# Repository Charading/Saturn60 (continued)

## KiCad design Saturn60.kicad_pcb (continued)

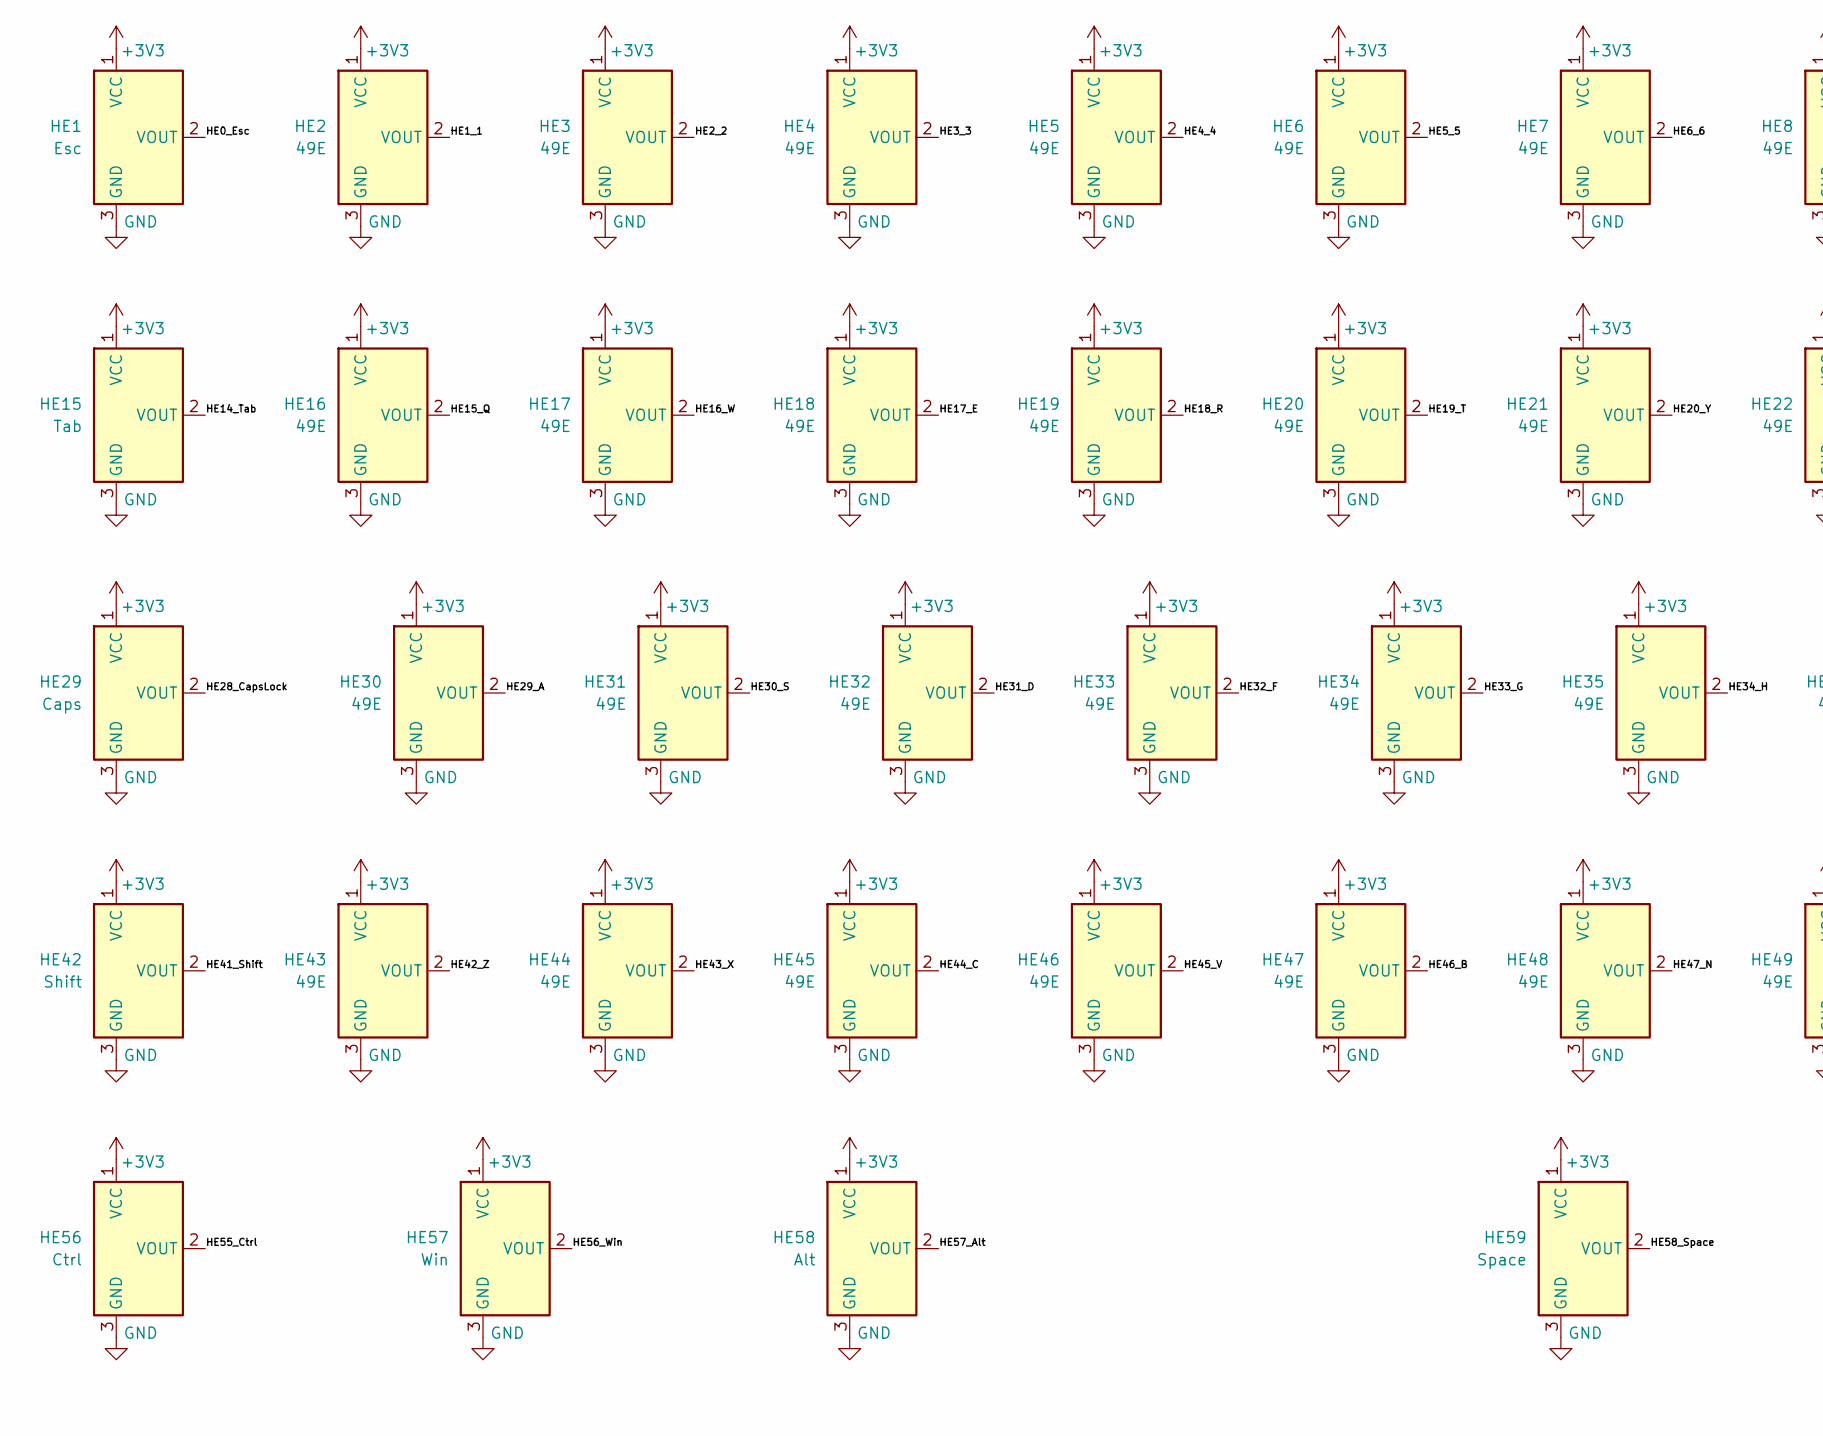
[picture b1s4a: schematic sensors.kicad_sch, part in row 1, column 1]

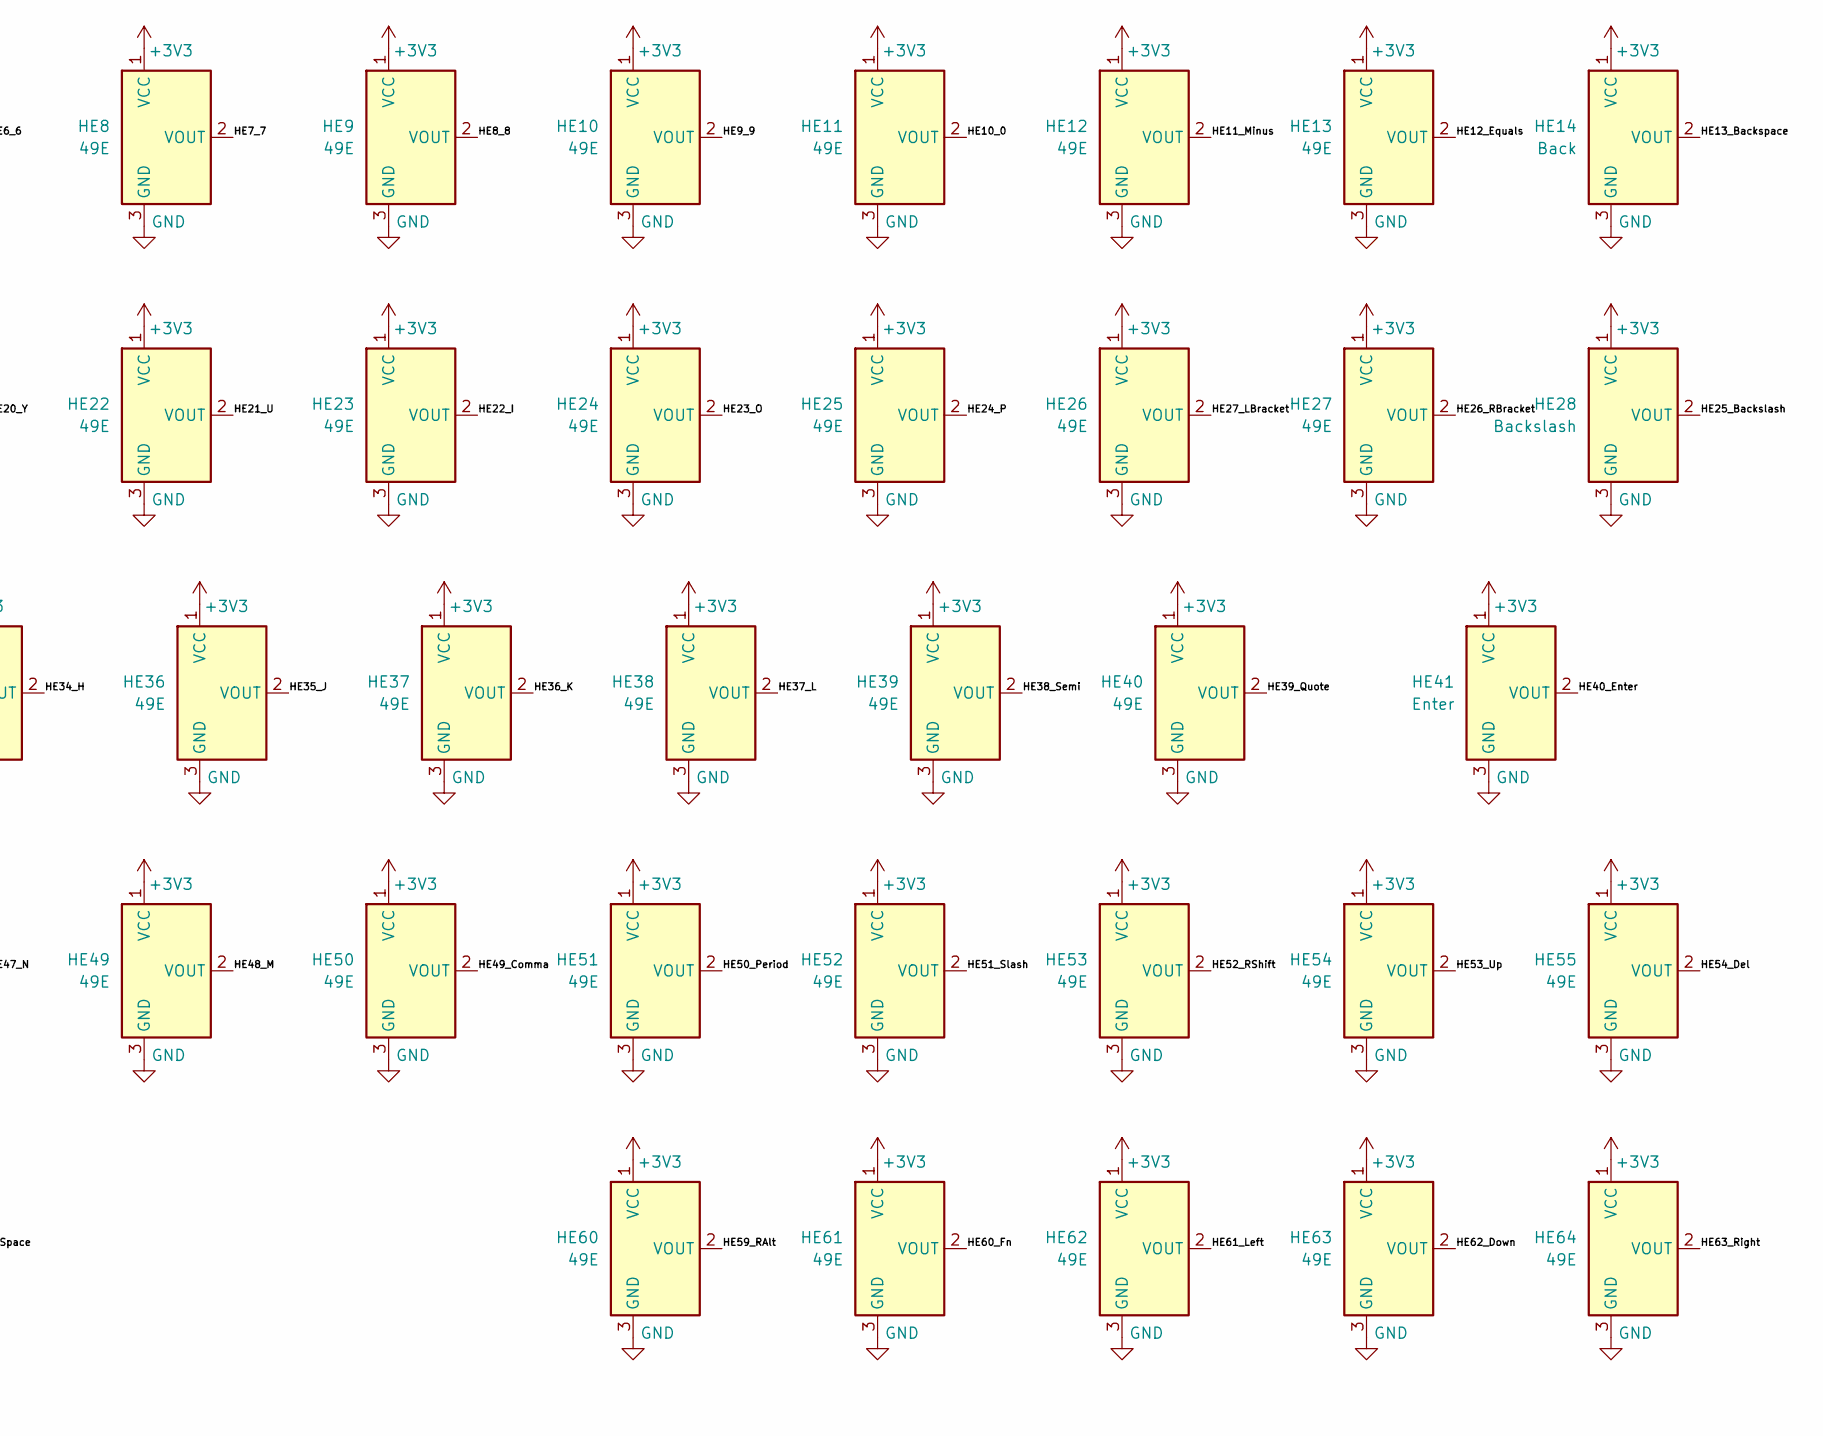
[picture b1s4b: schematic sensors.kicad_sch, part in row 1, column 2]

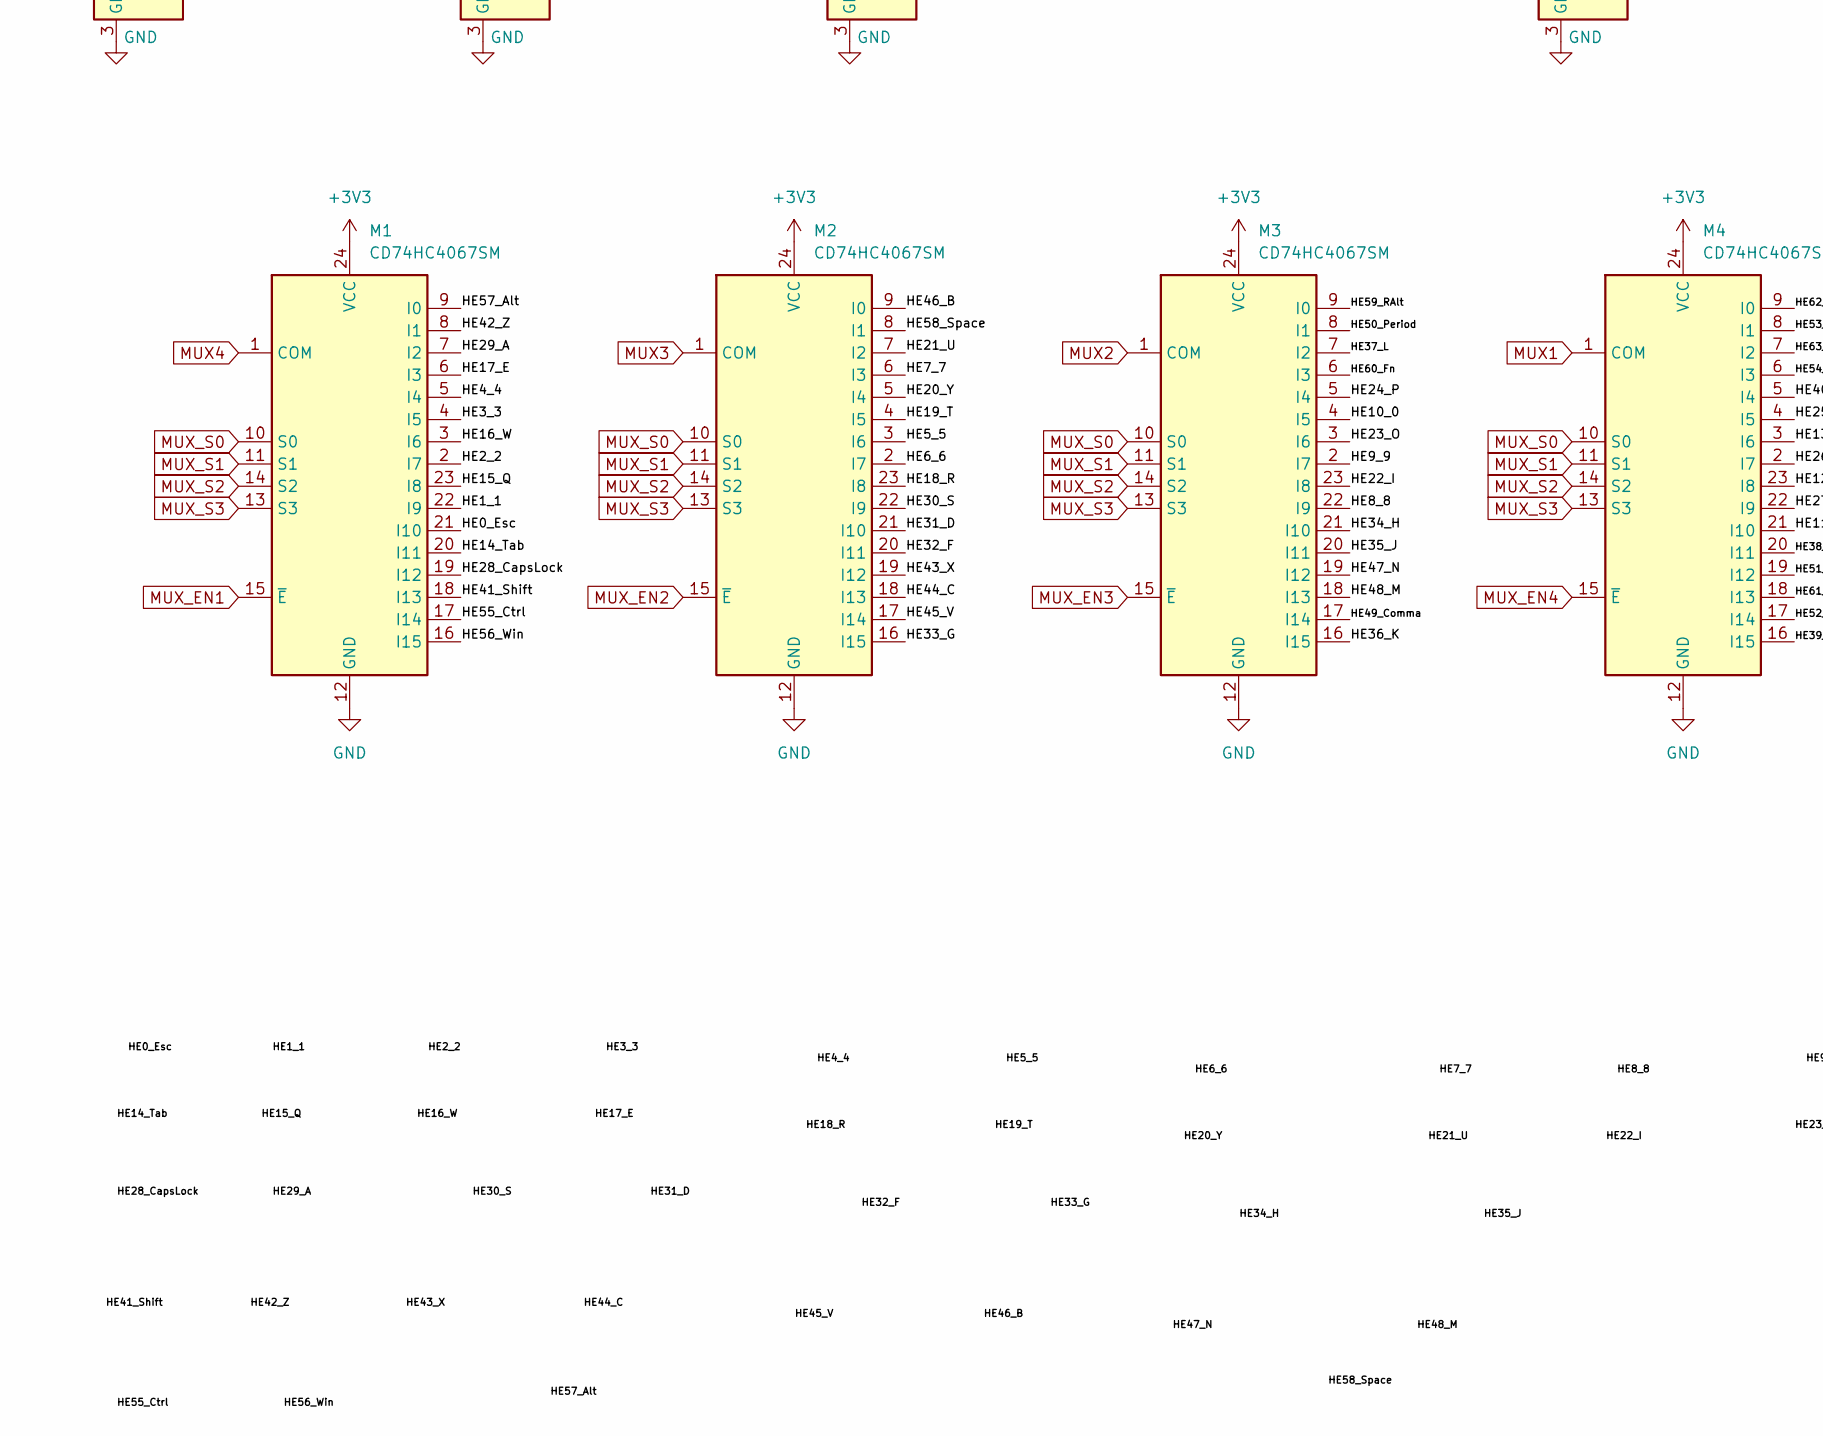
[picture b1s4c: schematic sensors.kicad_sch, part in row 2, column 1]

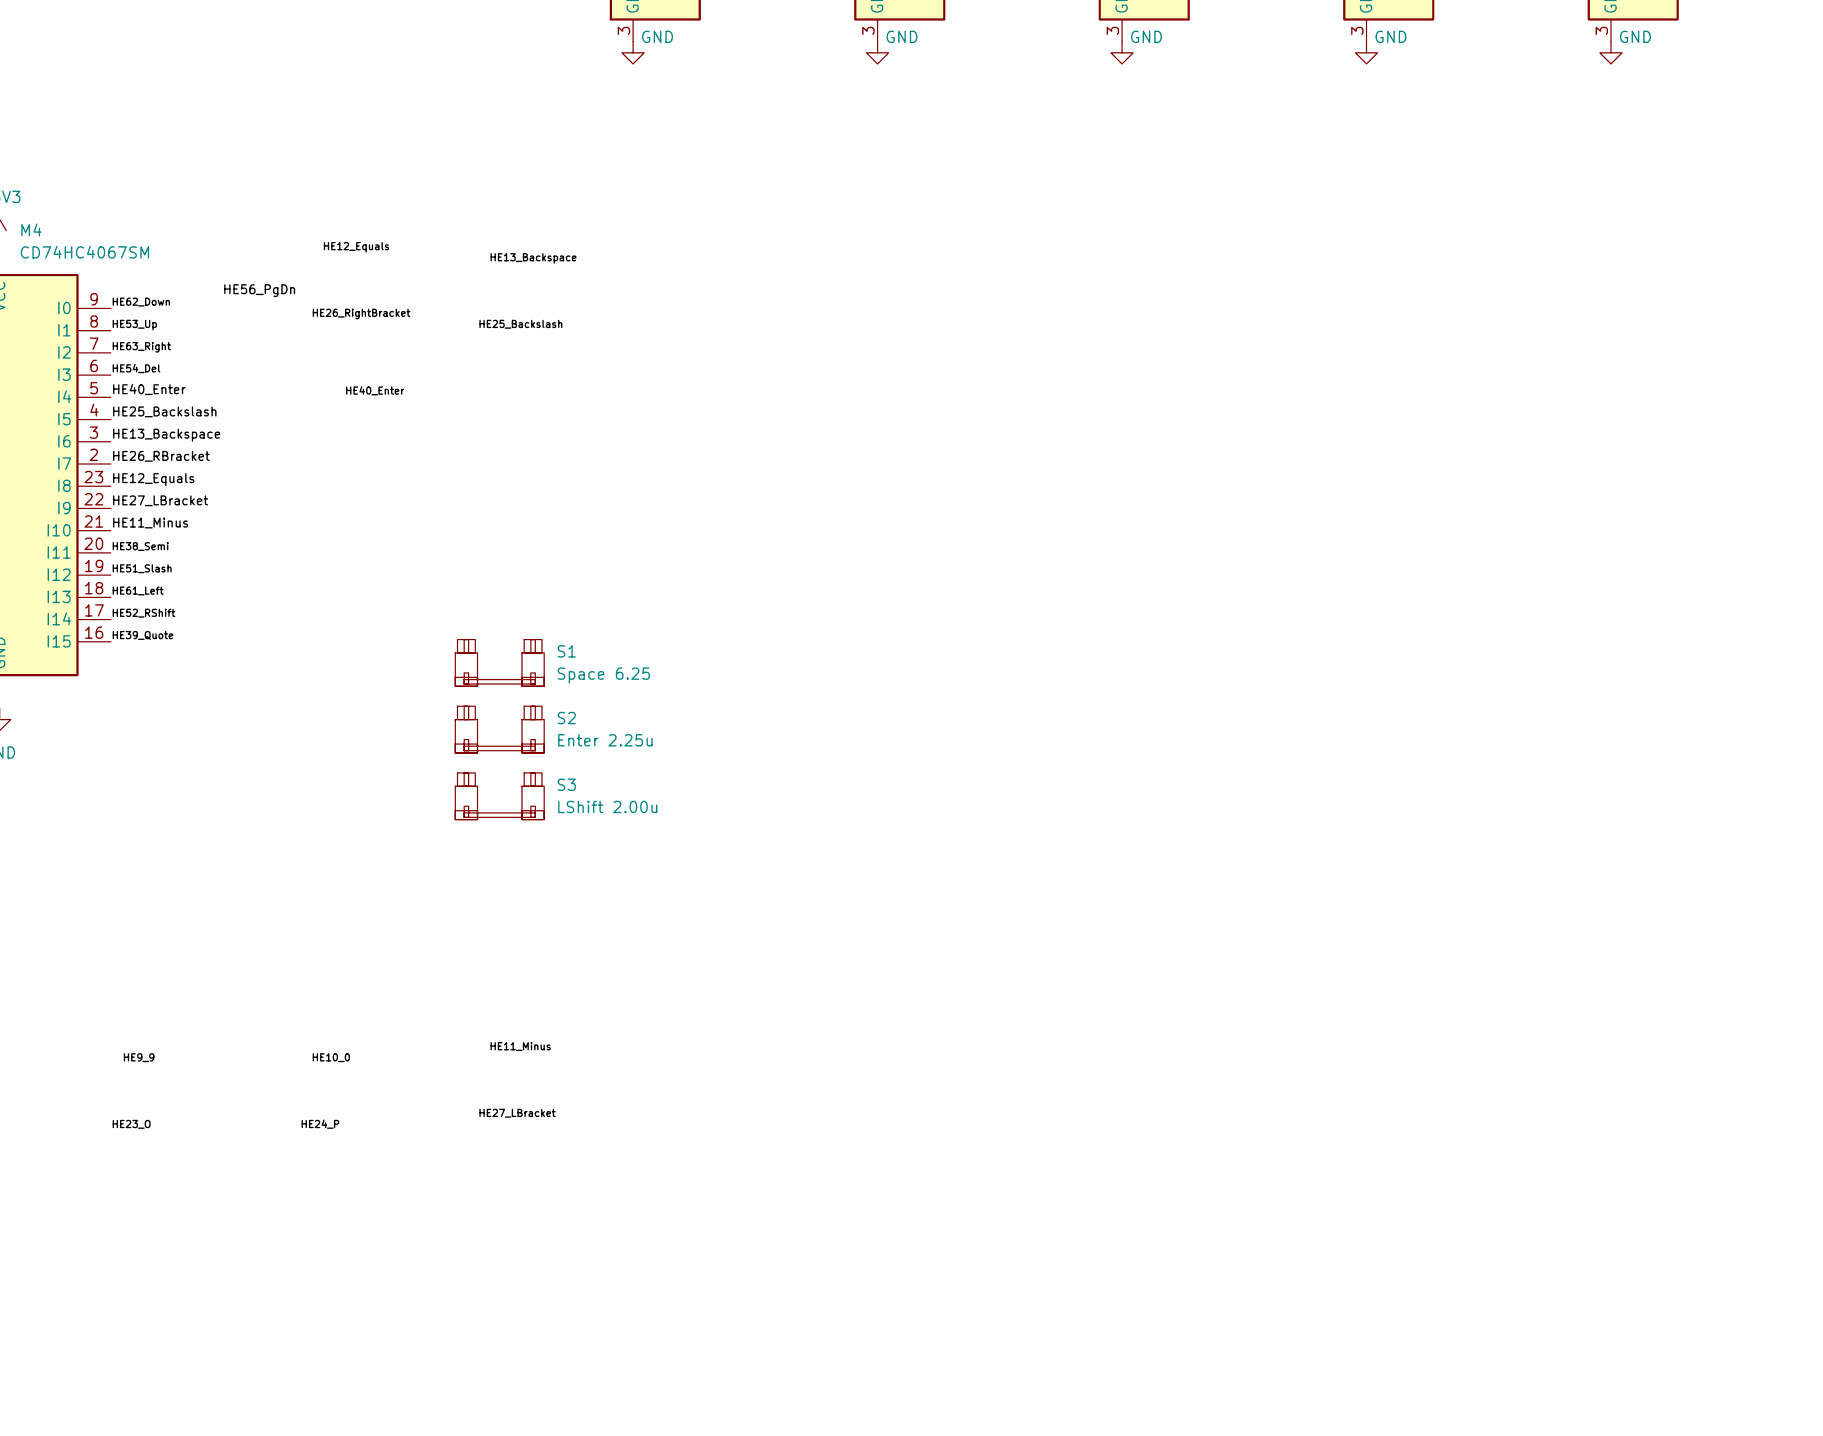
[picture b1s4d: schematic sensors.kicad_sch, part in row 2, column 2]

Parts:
HE1: Esc; SW_MX_HE_90deg_1u_Rules; LCSC C7420984
HE2, HE3, HE4, HE5, HE6, HE7, HE8, HE9, HE10, HE11, HE12, HE13, HE16, HE17, HE18, HE19, HE20, HE21, HE22, HE23, HE24, HE25, HE26, HE27, HE30, HE31, HE32, HE33, HE34, HE35, HE36, HE37, HE38, HE39, HE40, HE43, HE44, HE45, HE46, HE47, HE48, HE49, HE50, HE51, HE52, HE53, HE54, HE55, HE60, HE61, HE62, HE63, HE64: 49E; SW_MX_HE_90deg_1u_Rules; LCSC C7420984
HE14: Back; SW_MX_HE_90deg_1u_Rules; LCSC C7420984
HE15: Tab; SW_MX_HE_90deg_1.5u_Rules; LCSC C7420984
HE28: Backslash; SW_MX_HE_90deg_1.5u_Rules; LCSC C7420984
HE29: Caps; SW_MX_HE_90deg_1.75u_Rules; LCSC C7420984
HE41: Enter; SW_MX_HE_90deg_2.25u_Rules; LCSC C7420984
HE42: Shift; SW_MX_HE_90deg_2.00u_Rules; LCSC C7420984
HE56: Ctrl; SW_MX_HE_90deg_1.25u_Rules; LCSC C7420984
HE57: Win; SW_MX_HE_90deg_1.25u_Rules; LCSC C7420984
HE58: Alt; SW_MX_HE_90deg_1.25u_Rules; LCSC C7420984
HE59: Space; SW_MX_HE_90deg_6.25u_Rules; LCSC C7420984
M1, M2, M3, M4: CD74HC4067SM; SSOP-24_5.3x8.2mm_P0.65mm
S1: Space 6.25; STAB_MX_P_6.25u
S2: Enter 2.25u; STAB_MX_P_2.25u
S3: LShift 2.00u; STAB_MX_P_2u

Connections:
+3V3: HE1.1 (VCC), HE2.1 (VCC), HE3.1 (VCC), HE4.1 (VCC), HE5.1 (VCC), HE6.1 (VCC), HE7.1 (VCC), HE8.1 (VCC), HE9.1 (VCC), HE10.1 (VCC), HE11.1 (VCC), HE12.1 (VCC), HE13.1 (VCC), HE14.1 (VCC), HE15.1 (VCC), HE16.1 (VCC), HE17.1 (VCC), HE18.1 (VCC), HE19.1 (VCC), HE20.1 (VCC), HE21.1 (VCC), HE22.1 (VCC), HE23.1 (VCC), HE24.1 (VCC), HE25.1 (VCC), HE26.1 (VCC), HE27.1 (VCC), HE28.1 (VCC), HE29.1 (VCC), HE30.1 (VCC), HE31.1 (VCC), HE32.1 (VCC), HE33.1 (VCC), HE34.1 (VCC), HE35.1 (VCC), HE36.1 (VCC), HE37.1 (VCC), HE38.1 (VCC), HE39.1 (VCC), HE40.1 (VCC), HE41.1 (VCC), HE42.1 (VCC), HE43.1 (VCC), HE44.1 (VCC), HE45.1 (VCC), HE46.1 (VCC), HE47.1 (VCC), HE48.1 (VCC), HE49.1 (VCC), HE50.1 (VCC), HE51.1 (VCC), HE52.1 (VCC), HE53.1 (VCC), HE54.1 (VCC), HE55.1 (VCC), HE56.1 (VCC), HE57.1 (VCC), HE58.1 (VCC), HE59.1 (VCC), HE60.1 (VCC), HE61.1 (VCC), HE62.1 (VCC), HE63.1 (VCC), HE64.1 (VCC), M1.24 (VCC), M2.24 (VCC), M3.24 (VCC), M4.24 (VCC); also elsewhere on the board
/sensors/HE0_Esc: HE1.2 (VOUT), M1.21 (I10)
/sensors/HE1_1: HE2.2 (VOUT), M1.22 (I9)
/sensors/HE2_2: HE3.2 (VOUT), M1.2 (I7)
/sensors/HE3_3: HE4.2 (VOUT), M1.4 (I5)
/sensors/HE4_4: HE5.2 (VOUT), M1.5 (I4)
/sensors/HE5_5: HE6.2 (VOUT), M2.3 (I6)
/sensors/HE6_6: HE7.2 (VOUT), M2.2 (I7)
/sensors/HE7_7: HE8.2 (VOUT), M2.6 (I3)
/sensors/HE8_8: HE9.2 (VOUT), M3.22 (I9)
/sensors/HE9_9: HE10.2 (VOUT), M3.2 (I7)
/sensors/HE10_0: HE11.2 (VOUT), M3.4 (I5)
/sensors/HE11_Minus: HE12.2 (VOUT), M4.21 (I10)
/sensors/HE12_Equals: HE13.2 (VOUT), M4.23 (I8)
/sensors/HE13_Backspace: HE14.2 (VOUT), M4.3 (I6)
/sensors/HE14_Tab: HE15.2 (VOUT), M1.20 (I11)
/sensors/HE15_Q: HE16.2 (VOUT), M1.23 (I8)
/sensors/HE16_W: HE17.2 (VOUT), M1.3 (I6)
/sensors/HE17_E: HE18.2 (VOUT), M1.6 (I3)
/sensors/HE18_R: HE19.2 (VOUT), M2.23 (I8)
/sensors/HE19_T: HE20.2 (VOUT), M2.4 (I5)
/sensors/HE20_Y: HE21.2 (VOUT), M2.5 (I4)
/sensors/HE21_U: HE22.2 (VOUT), M2.7 (I2)
/sensors/HE22_I: HE23.2 (VOUT), M3.23 (I8)
/sensors/HE23_O: HE24.2 (VOUT), M3.3 (I6)
/sensors/HE24_P: HE25.2 (VOUT), M3.5 (I4)
/sensors/HE25_Backslash: HE28.2 (VOUT), M4.4 (I5)
/sensors/HE26_RBracket: HE27.2 (VOUT), M4.2 (I7)
/sensors/HE27_LBracket: HE26.2 (VOUT), M4.22 (I9)
/sensors/HE28_CapsLock: HE29.2 (VOUT), M1.19 (I12)
/sensors/HE29_A: HE30.2 (VOUT), M1.7 (I2)
/sensors/HE30_S: HE31.2 (VOUT), M2.22 (I9)
/sensors/HE31_D: HE32.2 (VOUT), M2.21 (I10)
/sensors/HE32_F: HE33.2 (VOUT), M2.20 (I11)
/sensors/HE33_G: HE34.2 (VOUT), M2.16 (I15)
/sensors/HE34_H: HE35.2 (VOUT), M3.21 (I10)
/sensors/HE35_J: HE36.2 (VOUT), M3.20 (I11)
/sensors/HE36_K: HE37.2 (VOUT), M3.16 (I15)
/sensors/HE37_L: HE38.2 (VOUT), M3.7 (I2)
/sensors/HE38_Semi: HE39.2 (VOUT), M4.20 (I11)
/sensors/HE39_Quote: HE40.2 (VOUT), M4.16 (I15)
/sensors/HE40_Enter: HE41.2 (VOUT), M4.5 (I4)
/sensors/HE41_Shift: HE42.2 (VOUT), M1.18 (I13)
/sensors/HE42_Z: HE43.2 (VOUT), M1.8 (I1)
/sensors/HE43_X: HE44.2 (VOUT), M2.19 (I12)
/sensors/HE44_C: HE45.2 (VOUT), M2.18 (I13)
/sensors/HE45_V: HE46.2 (VOUT), M2.17 (I14)
/sensors/HE46_B: HE47.2 (VOUT), M2.9 (I0)
/sensors/HE47_N: HE48.2 (VOUT), M3.19 (I12)
/sensors/HE48_M: HE49.2 (VOUT), M3.18 (I13)
/sensors/HE49_Comma: HE50.2 (VOUT), M3.17 (I14)
/sensors/HE50_Period: HE51.2 (VOUT), M3.8 (I1)
/sensors/HE51_Slash: HE52.2 (VOUT), M4.19 (I12)
/sensors/HE52_RShift: HE53.2 (VOUT), M4.17 (I14)
/sensors/HE53_Up: HE54.2 (VOUT), M4.8 (I1)
/sensors/HE54_Del: HE55.2 (VOUT), M4.6 (I3)
/sensors/HE55_Ctrl: HE56.2 (VOUT), M1.17 (I14)
/sensors/HE56_Win: HE57.2 (VOUT), M1.16 (I15)
/sensors/HE57_Alt: HE58.2 (VOUT), M1.9 (I0)
/sensors/HE58_Space: HE59.2 (VOUT), M2.8 (I1)
/sensors/HE59_RAlt: HE60.2 (VOUT), M3.9 (I0)
/sensors/HE60_Fn: HE61.2 (VOUT), M3.6 (I3)
/sensors/HE61_Left: HE62.2 (VOUT), M4.18 (I13)
/sensors/HE62_Down: HE63.2 (VOUT), M4.9 (I0)
/sensors/HE63_Right: HE64.2 (VOUT), M4.7 (I2)
GND: HE1.3 (GND), HE2.3 (GND), HE3.3 (GND), HE4.3 (GND), HE5.3 (GND), HE6.3 (GND), HE7.3 (GND), HE8.3 (GND), HE9.3 (GND), HE10.3 (GND), HE11.3 (GND), HE12.3 (GND), HE13.3 (GND), HE14.3 (GND), HE15.3 (GND), HE16.3 (GND), HE17.3 (GND), HE18.3 (GND), HE19.3 (GND), HE20.3 (GND), HE21.3 (GND), HE22.3 (GND), HE23.3 (GND), HE24.3 (GND), HE25.3 (GND), HE26.3 (GND), HE27.3 (GND), HE28.3 (GND), HE29.3 (GND), HE30.3 (GND), HE31.3 (GND), HE32.3 (GND), HE33.3 (GND), HE34.3 (GND), HE35.3 (GND), HE36.3 (GND), HE37.3 (GND), HE38.3 (GND), HE39.3 (GND), HE40.3 (GND), HE41.3 (GND), HE42.3 (GND), HE43.3 (GND), HE44.3 (GND), HE45.3 (GND), HE46.3 (GND), HE47.3 (GND), HE48.3 (GND), HE49.3 (GND), HE50.3 (GND), HE51.3 (GND), HE52.3 (GND), HE53.3 (GND), HE54.3 (GND), HE55.3 (GND), HE56.3 (GND), HE57.3 (GND), HE58.3 (GND), HE59.3 (GND), HE60.3 (GND), HE61.3 (GND), HE62.3 (GND), HE63.3 (GND), HE64.3 (GND), M1.12 (GND), M2.12 (GND), M3.12 (GND), M4.12 (GND); also elsewhere on the board
MUX1: M4.1 (COM); also elsewhere on the board
MUX2: M3.1 (COM); also elsewhere on the board
MUX3: M2.1 (COM); also elsewhere on the board
MUX4: M1.1 (COM); also elsewhere on the board
MUX_EN1: M1.15 (~E); also elsewhere on the board
MUX_EN2: M2.15 (~E); also elsewhere on the board
MUX_EN3: M3.15 (~E); also elsewhere on the board
MUX_EN4: M4.15 (~E); also elsewhere on the board
MUX_S0: M1.10 (S0), M2.10 (S0), M3.10 (S0), M4.10 (S0); also elsewhere on the board
MUX_S1: M1.11 (S1), M2.11 (S1), M3.11 (S1), M4.11 (S1); also elsewhere on the board
MUX_S2: M1.14 (S2), M2.14 (S2), M3.14 (S2), M4.14 (S2); also elsewhere on the board
MUX_S3: M1.13 (S3), M2.13 (S3), M3.13 (S3), M4.13 (S3); also elsewhere on the board

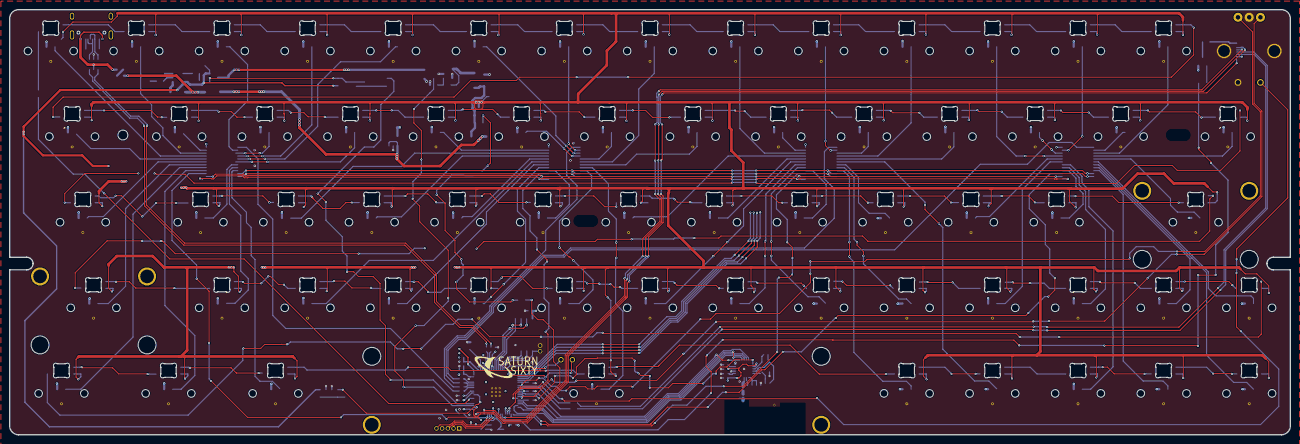
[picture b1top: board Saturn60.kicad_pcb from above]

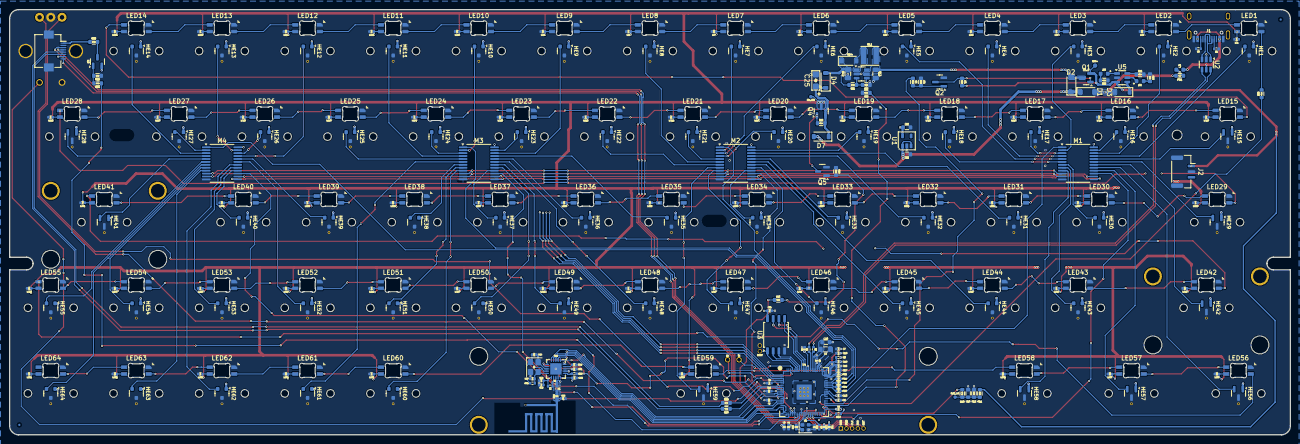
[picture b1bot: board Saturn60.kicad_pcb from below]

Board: 4 copper layers, 285.0 x 94.6 mm, 314 parts (310 on the bottom side), 228 nets.

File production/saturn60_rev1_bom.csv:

Designator,Footprint,Quantity,Value,LCSC Part #
ANT1,MIFA_2.4GHz_Antenna,1,2.4GHz,
"BC1, BC2",C_0805,2,22uF,
"BD4, D1, D2, D3, D4, D7",D_SOD-123,6,1N5819M,
BL1,L_Taiyo-Yuden_NR-40xx,1,10uH,
BR1,R_0603,1,750K,
"BR2, BR3, R16, R17, R22, R6",R_0603,6,100K,
BU1,SOT-23-6,1,MT3608,
"C1, C11, C12, C16, C2, C7, C8, C9",C_0402,8,100nF,C1525
C10,C_0603,1,100nF,C14663
"C13, C24, C3",C_0402,3,100nF,C14663
"C14, C15, C20",C_0603,3,4.7uF,
C17,C_0402,1,10uF,C1525
"C18, C19",C_0402,2,4.7uF,
"C21, C4, C5, C6",C_0402,4,100nF,
"C22, C23",C_0402,2,15pF,
C25,CP_EIA-3216-10_Kemet-I,1,47uF,
CC1,C_0402,1,10nF,
CC2,C_0402,1,1nF,
CC3,C_0402,1,2.2nF,
CC4,C_0402,1,4.7pF,
CC5,C_0402,1,1.5pF,
CC6,C_0402,1,1pF,
"CC7, CC8",C_0402,2,22pF,
CC9,C_0402,1,33nF,
D5,Mars_LED_0603,1,RED,
D6,Mars_LED_0603,1,BLU,
ENC1,RotaryEncoder_MX_EC11_CircularMountingHoles,1,RotaryEncoder_Switch,
F1,0603,1,1.1A,
FB1,Ferrite_0603,1,600R,
FB2,Ferrite_0402,1,600R,
"FB3, FB4, FB5, FB6",Ferrite_0402,4,100R,
HE1,SW_MX_HE_90deg_1u_Rules,1,Esc,C7420984
"HE10, HE11, HE12, HE13, HE16, HE17, HE18, HE19, HE2, HE20, HE21, HE22, HE23, HE24, HE25, HE26, HE27, HE3, HE30, HE31, HE32, HE33, HE34, HE35, HE36, HE37, HE38, HE39, HE4, HE40, HE43, HE44, HE45, HE46, HE47, HE48, HE49, HE5, HE50, HE51, HE52, HE53, HE54, HE55, HE6, HE60, HE61, HE62, HE63, HE64, HE7, HE8, HE9",SW_MX_HE_90deg_1u_Rules,53,49E,C7420984
HE14,SW_MX_HE_90deg_1u_Rules,1,Back,C7420984
HE15,SW_MX_HE_90deg_1.5u_Rules,1,Tab,C7420984
HE28,SW_MX_HE_90deg_1.5u_Rules,1,Backslash,C7420984
HE29,SW_MX_HE_90deg_1.75u_Rules,1,Caps,C7420984
HE41,SW_MX_HE_90deg_2.25u_Rules,1,Enter,C7420984
HE42,SW_MX_HE_90deg_2.00u_Rules,1,Shift,C7420984
HE56,SW_MX_HE_90deg_1.25u_Rules,1,Ctrl,C7420984
HE57,SW_MX_HE_90deg_1.25u_Rules,1,Win,C7420984
HE58,SW_MX_HE_90deg_1.25u_Rules,1,Alt,C7420984
HE59,SW_MX_HE_90deg_6.25u_Rules,1,Space,C7420984
J1,USB_C_Receptacle_HRO_TYPE-C-31-M-12 (16P),1,USB_C_Receptacle,
J2,JST_GH_SM03B-GHS-TB_1x03-1MP_P1.25mm_Horizontal,1,BATTERY,
J3,TFT_FPC_8P_0.5mm,1,TFT,
L1,R_0402,1,8.2nH,
L2,R_0402,1,2.7nH,
L3,R_0402,1,3.9nH,
L4,0805,1,3.3uH,
"LC1, LC10, LC11, LC12, LC13, LC14, LC15, LC16, LC17, LC18, LC19, LC2, LC20, LC21, LC22, LC23, LC24, LC25, LC26, LC27, LC28, LC29, LC3, LC30, LC31, LC32, LC33, LC34, LC35, LC36, LC37, LC38, LC39, LC4, LC40, LC41, LC42, LC43, LC44, LC45, LC46, LC47, LC48, LC49, LC5, LC50, LC51, LC52, LC53, LC54, LC55, LC56, LC57, LC58, LC59, LC6, LC60, LC61, LC62, LC63, LC64, LC7, LC8, LC9",C_0402,64,0.1uF,
"LED1, LED10, LED11, LED12, LED13, LED14, LED15, LED16, LED17, LED18, LED19, LED2, LED20, LED21, LED22, LED23, LED24, LED25, LED26, LED27, LED28, LED29, LED3, LED30, LED31, LED32, LED33, LED34, LED35, LED36, LED37, LED38, LED39, LED4, LED40, LED41, LED42, LED43, LED44, LED45, LED46, LED47, LED48, LED49, LED5, LED50, LED51, LED52, LED53, LED54, LED55, LED56, LED57, LED58, LED59, LED6, LED60, LED61, LED62, LED63, LED64, LED7, LED8, LED9",LED_6028R,64,SK6812MINI-E,C5149201 
"M1, M2, M3, M4",SSOP-24_5.3x8.2mm_P0.65mm,4,CD74HC4067SM,
"Q1, Q3, Q4",SOT-23,3,AO3401A,
"Q2, Q5",SOT-23,2,BSS138,
"R1, R2",R_0402,2,5.1K,
"R10, R14, R15",R_0603,3,3.3K,
"R11, R12",R_0603,2,300K,
R13,R_0402,1,10K,
"R18, R8",R_0603,2,1M,
R19,R_0603,1,330R,
R20,R_0603,1,100R,
R21,R_0603,1,100,
R23,R_0603,1,47,
"R24, R25",R_0603,2,33R,
R3,R_0402,1,33R,
"R4, R5",R_0402,2,27R,
R7,R_0603,1,10K,
R9,R_0402,1,1K,
RR1,R_0402,1,1M,
RR2,R_0402,1,22K,
S1,STAB_MX_P_6.25u,1,Space 6.25,
S2,STAB_MX_P_2.25u,1,Enter 2.25u,
S3,STAB_MX_P_2u,1,LShift 2.00u,
SWD1,SWD_Debug_PinHeader_1x05_P1.27mm,1,DEBUG,
TP1,TestPoint_2Pads_Pitch2.54mm_Drill0.8mm,1,BOOT,
TP2,TestPoint_Pad_D1.0mm_Minimal,1,BAT,
TP3,TestPoint_Pad_D1.0mm_Minimal,1,5V,
TP4,TestPoint_Pad_D1.0mm_Minimal,1,BAT_LVL,
TP5,TestPoint_Pad_D1.0mm_Minimal,1,GP0,
TP6,TestPoint_Pad_D1.0mm_Minimal,1,GP1,
U1,SOT-23-5,1,AP2112K-3.3TRG1,
U11,QFN-20-1EP_4x4mm_P0.5mm_EP2.5x2.5mm,1,nRF24L01P,
U2,SOT-23-6,1,USBLC6-2SC6,
U3,SOIC-8_5.3x5.3mm_P1.27mm,1,W25Q128JVS,C97521
U4,RP2350B_QFN-80_EP_10.573x10.573_Pitch0.4mm,1,RP2350B-QFN80,
U5,TSOT-23-6,1,TP4057,
Y1,Crystal_SMD_2016-4Pin_2.0x1.6mm,1,12MHz,
Y2,Crystal_SMD_3225-4Pin_3.2x2.5mm,1,16MHz,

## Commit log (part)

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2026-02-06 Initial Saturn60 hardware
